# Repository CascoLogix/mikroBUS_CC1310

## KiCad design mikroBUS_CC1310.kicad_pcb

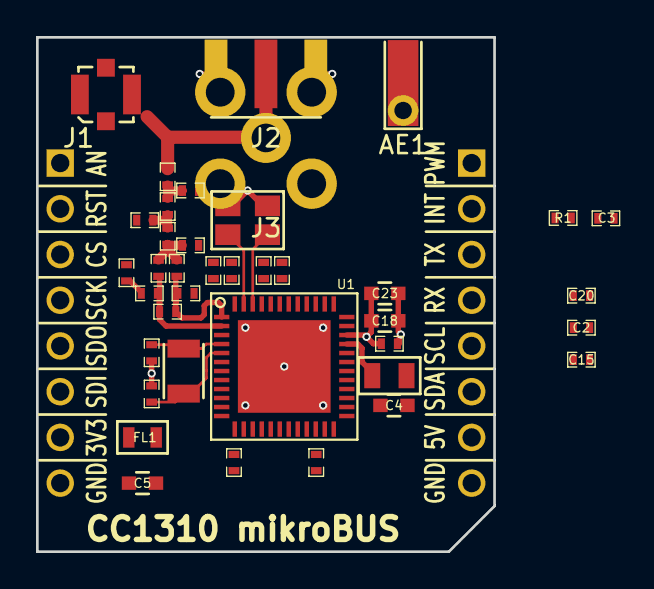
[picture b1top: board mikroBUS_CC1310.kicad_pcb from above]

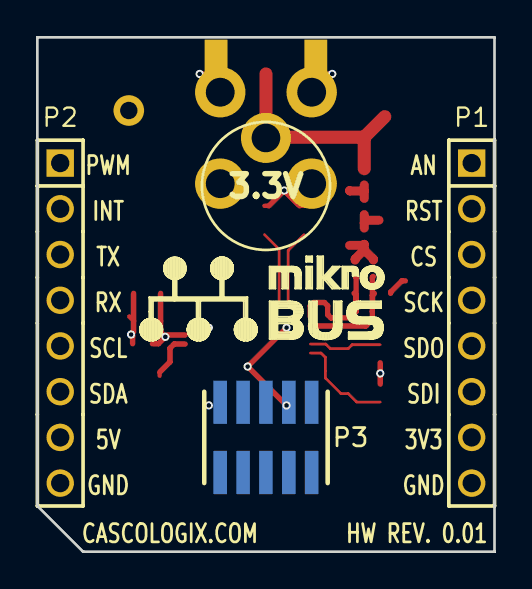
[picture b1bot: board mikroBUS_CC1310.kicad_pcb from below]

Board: 4 copper layers, 25.4 x 28.6 mm, 42 parts (3 on the bottom side), 33 nets.

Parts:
AE1: 915MHz Spring; ANTENNA_HELICAL_RA
C1, C6: 12pF; 0402
C2: 1uF; 0402
C3, C8, C9, C12, C13, C17, C21: 100nF; 0402
C4, C18: 22uF; C_0603
C5, C23: DNP; C_0603
C7, C11: 3.6pF; 0402
C10, C24: 100pF; 0402
C14: 2.7pF; 0402
C15, C16, C20: DNP; 0402
C19: 6.2pF; 0402
C22: 3pF; 0402
FL1: BLM18HE152SN1; 0603
J1: u.FL; U.FL-R-SMT
J2: SMA; SMA_EDGE
J3: SMA Straight; SMA_STRAIGHT_SOCKET
L1: 27nH; 0402
L2: 6.8uH; 0805
L4, L5: 7.5nH; 0402
L6, L7: 6.8nH; 0402
P1, P2: HEADER_M_2.54MM_1R8P_ST_AU_PTH
P3: JTAG; HEADER_50MIL_2R10P_SMT
R1: 100k; 0402
U1: CC1310F128RGZ; VQFN-48
Y1: 32.768kHz; FC_135
Y2: 24MHz; SX_3225

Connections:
+3.3V: FL1.1, P1.7, P3.1
/RF_Match1: C11.1, C14.1, L5.1, L6.2
/RF_Match2: C19.1, L6.1, L7.2
/RF_Match3: C22.1, C24.2, L7.1
AN: P1.1, U1.6
ANT: AE1.1, C24.1, J1.1, J2.1, J3.1
CS: P1.3, U1.7
DCDC_SW: L2.1, U1.33
GND: C1.2, C2.2, C3.2, C4.2, C5.2, C6.2, C7.2, C8.2, C9.2, C10.1, C12.2, C13.2, C14.2, C15.2, C16.2, C17.2, C18.2, C19.2, C20.2, C21.2, C22.2, C23.2, J1.2, J1.3, J1.4, J2.2, J2.3, J3.2, J3.3, J3.4, J3.5, P1.8, P2.8, P3.8, U1.49, Y2.3, Y2.4
INT: P2.2, U1.12
JTAG_TCK: P3.4, U1.25
JTAG_TDI: P3.7, U1.27
JTAG_TDO: P3.5, U1.26
JTAG_TMS: P3.2, U1.24
MISO: P1.5, U1.9
MOSI: P1.6, U1.10
unnamed: C2.1, U1.23
PWM: P2.1, U1.11
RF_N: C11.2, L1.2, L4.1, U1.2
RF_P: C7.1, L1.1, L5.2, U1.1
RF_RXTX: C10.2, L4.2, U1.3
RX: P2.3, U1.14
SCK: P1.4, U1.8
SCL: P2.5, U1.16
SDA: P2.6, U1.17
TX: P2.4, U1.15
VDD: C5.1, C9.1, C13.1, C17.1, C18.1, C21.1, C23.1, FL1.2, R1.2, U1.13, U1.22, U1.34, U1.44
VEE: C4.1, C8.1, C12.1, C16.1, L2.2, U1.45, U1.48
X24M_N: C20.1, U1.46, Y2.2
X24M_P: C15.1, U1.47, Y2.1
X32K_Q1: C1.1, U1.4, Y1.1
X32K_Q2: C6.1, U1.5, Y1.2
nRESET: C3.1, P1.2, P3.3, R1.1, U1.35

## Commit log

2015-12-05 First commit.
2015-12-13 Some progress in layout.
2015-12-23 Layout for RF impedance match network completed. Added spring antenna and through-hole SMA straight connector as options.
